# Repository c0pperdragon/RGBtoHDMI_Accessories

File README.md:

# RGBtoHDMI_Accessories

Some simple hardware parts to work together with the RGBtoHDMI.

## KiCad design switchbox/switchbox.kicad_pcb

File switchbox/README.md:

# Switchbox

Mechanical switchbox to select one of two 6-pin inputs to be forwarded to one Analog RGBtoHDMI.

Note that only the 3 color signals and the csync is switched. The GND and +5V pins are always 
connected through. Therefore do not connect two cables that provide their +5V to the RGBtoHDMI 
at the same time, as these would then be shorted together, which could damage either or 
both of the connected machines.

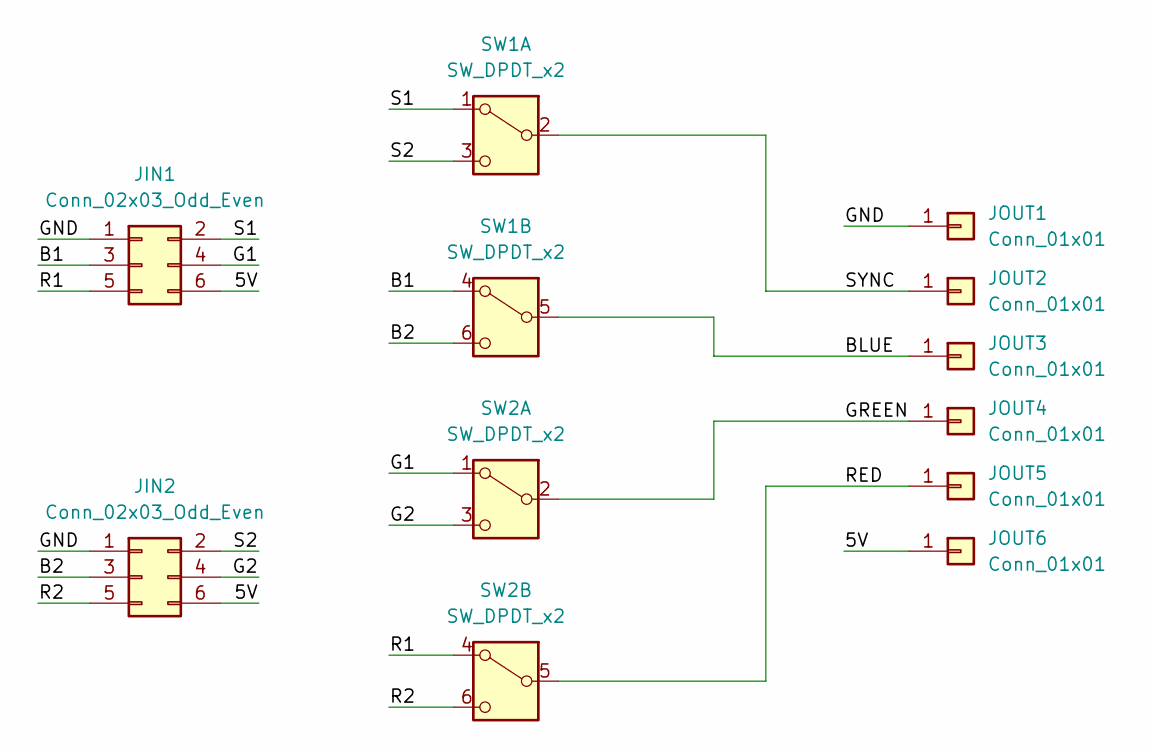
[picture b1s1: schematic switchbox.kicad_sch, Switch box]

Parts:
JIN1, JIN2: Conn_02x03_Odd_Even; IDC_PCB_mount_6
JOUT1, JOUT2, JOUT3, JOUT4, JOUT5, JOUT6: Conn_01x01; TestPoint_Pad_1.5x2.5mm
SW1, SW2: SW_DPDT_x2; OS202011MS2QN1

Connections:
/5V: JIN1.6, JIN2.6, JOUT6.1
/B1: JIN1.3, SW1.4 (A)
/B2: JIN2.3, SW1.6 (C)
/BLUE: JOUT3.1, SW1.5 (B)
/G1: JIN1.4, SW2.1 (A)
/G2: JIN2.4, SW2.3 (C)
/GND: JIN1.1, JIN2.1, JOUT1.1
/GREEN: JOUT4.1, SW2.2 (B)
/R1: JIN1.5, SW2.4 (A)
/R2: JIN2.5, SW2.6 (C)
/RED: JOUT5.1, SW2.5 (B)
/S1: JIN1.2, SW1.1 (A)
/S2: JIN2.2, SW1.3 (C)
/SYNC: JOUT2.1, SW1.2 (B)

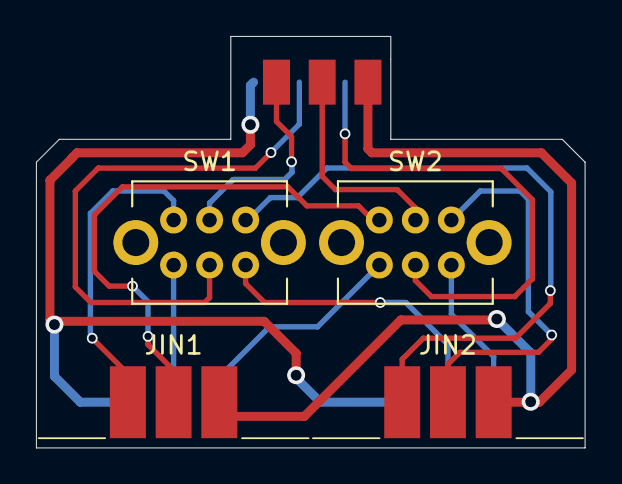
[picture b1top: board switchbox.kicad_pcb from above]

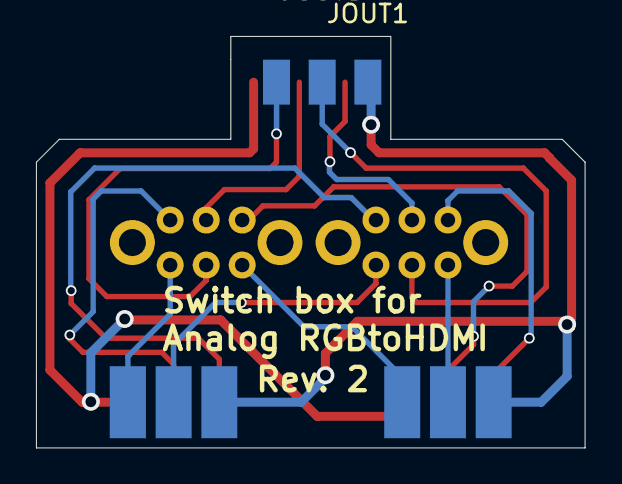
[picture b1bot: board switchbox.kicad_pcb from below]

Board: 2 copper layers, 30.5 x 22.9 mm, 10 parts (3 on the bottom side), 14 nets.

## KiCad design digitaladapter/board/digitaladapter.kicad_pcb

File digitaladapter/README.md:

# Digital adapter

This is a bridge from machines using a DB9 connector with
digital video output (MDA, CGA, EGA, C128) to the Analog RGBtoHDMI.

Up to 6 digital color signals are merged into 3 analog lines carrying one of 4 voltages. 
Separate sync signals are also XOR-merged to create composite sync.

For its active circuitry to work, it needs to draw a small amount of power
from the +5V pin of the 6-pin IDC connector. As this is normally not supported
by the RGBtoHDMI, one small modification is necessary to the analog board.

Until the offical RGBtoHDMI software directly provides working profiles, you need to 
add the files from 
[this archive](db9toanalog_extrafiles_2.zip)
to the installation.

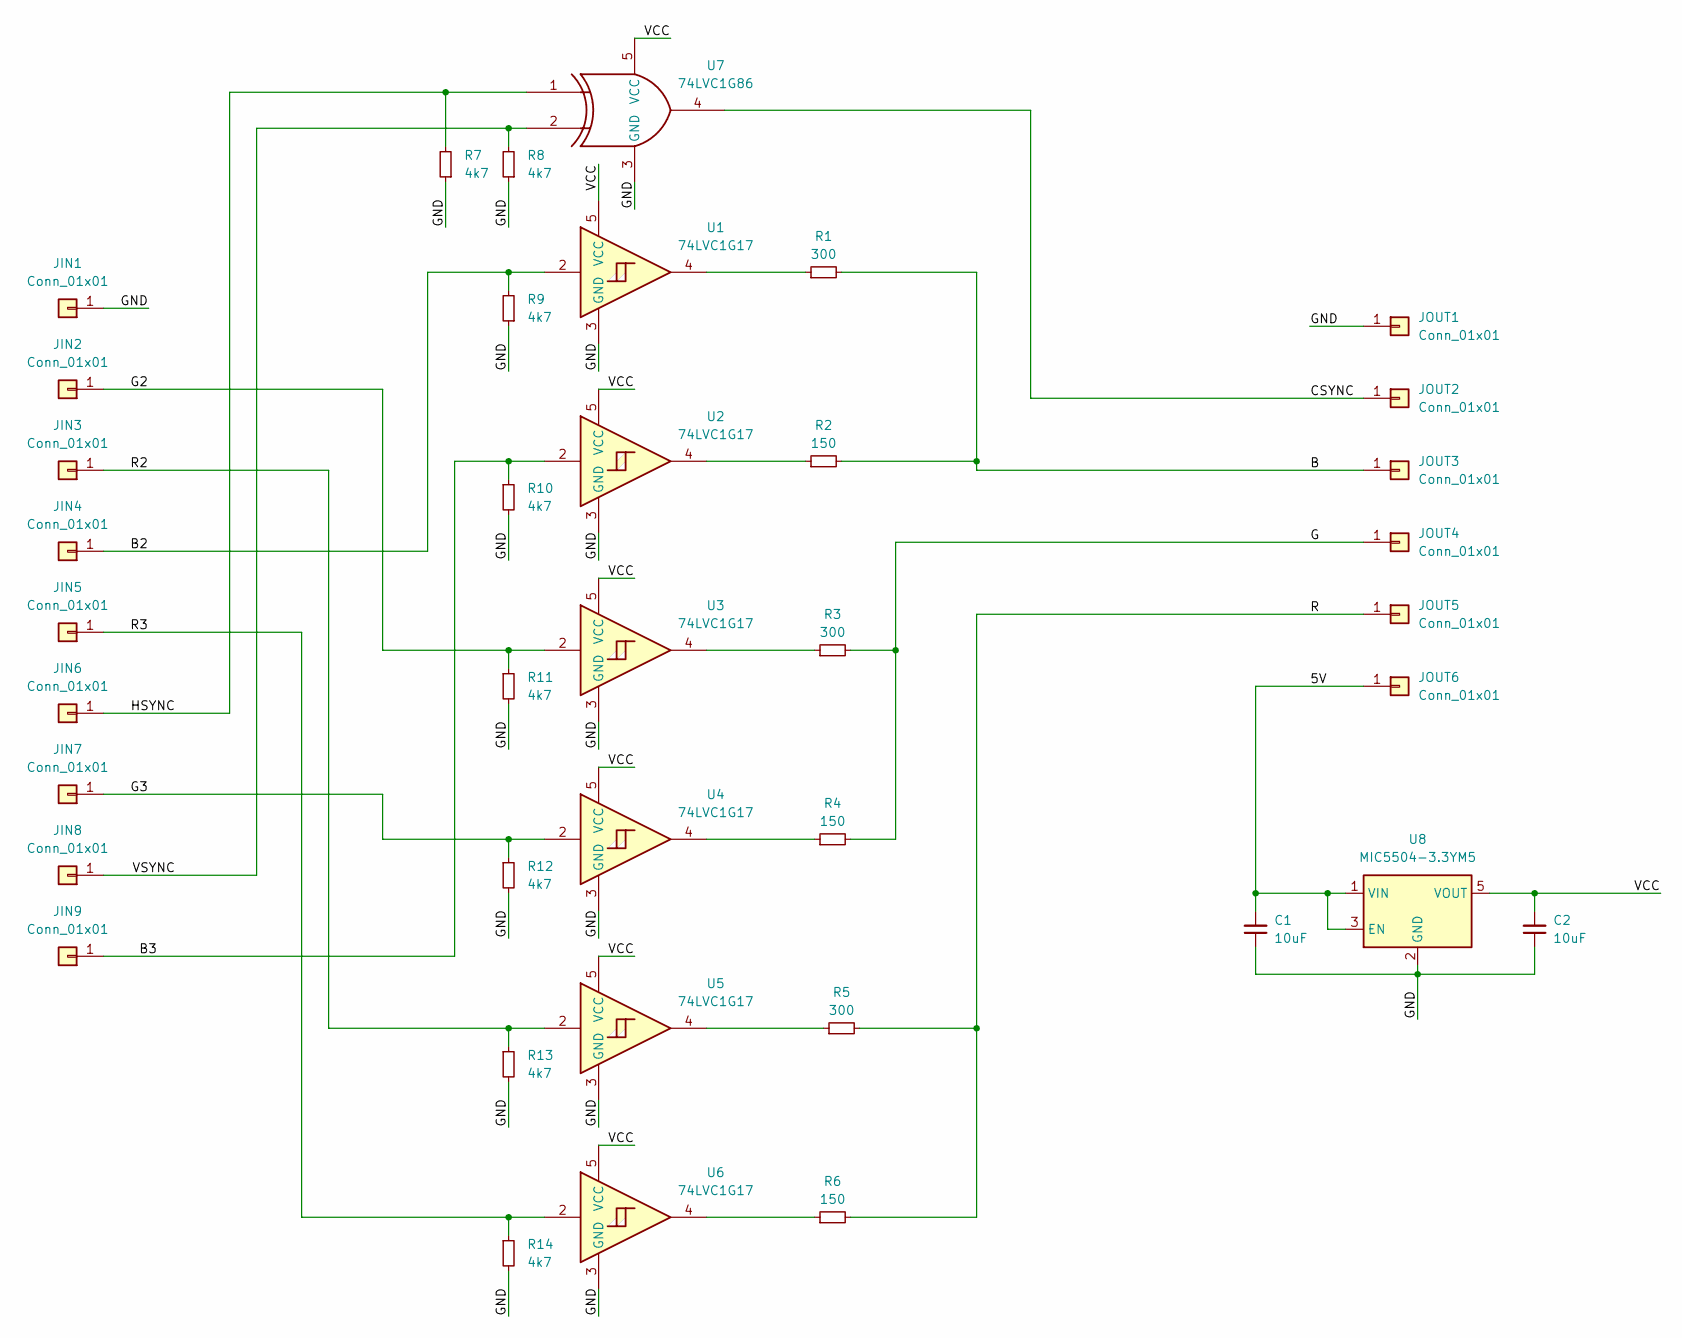
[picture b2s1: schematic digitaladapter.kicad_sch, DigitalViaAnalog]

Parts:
C1, C2: 10uF; C_0805_2012Metric
JIN1, JIN2, JIN3, JIN4, JIN5, JIN6, JIN7, JIN8, JIN9: Conn_01x01; TestPoint_Pad_2.5x1.5mm
JOUT1, JOUT2, JOUT3, JOUT4, JOUT5, JOUT6: Conn_01x01; TestPoint_Pad_2.5x1.5mm
R1, R3, R5: 300; R_0603_1608Metric
R2, R4, R6: 150; R_0603_1608Metric
R7, R8, R9, R10, R11, R12, R13, R14: 4k7; R_0603_1608Metric
U1, U2, U3, U4, U5, U6: 74LVC1G17; SOT-353_SC-70-5
U7: 74LVC1G86; SOT-353_SC-70-5
U8: MIC5504-3.3YM5; SOT-23-5

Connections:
/5V: C1.2, JOUT6.1, U8.1 (VIN), U8.3 (EN)
/B: JOUT3.1, R1.2, R2.2
/B2: JIN4.1, R9.2, U1.2
/B3: JIN9.1, R10.1, U2.2
/CSYNC: JOUT2.1, U7.4
/G: JOUT4.1, R3.2, R4.2
/G2: JIN2.1, R11.1, U3.2
/G3: JIN7.1, R12.1, U4.2
/GND: C1.1, C2.1, JIN1.1, JOUT1.1, R7.1, R8.1, R9.1, R10.2, R11.2, R12.2, R13.2, R14.2, U1.3 (GND), U2.3 (GND), U3.3 (GND), U4.3 (GND), U5.3 (GND), U6.3 (GND), U7.3 (GND), U8.2 (GND)
/HSYNC: JIN6.1, R7.2, U7.1
/R: JOUT5.1, R5.2, R6.2
/R2: JIN3.1, R13.1, U5.2
/R3: JIN5.1, R14.1, U6.2
/VCC: C2.2, U1.5 (VCC), U2.5 (VCC), U3.5 (VCC), U4.5 (VCC), U5.5 (VCC), U6.5 (VCC), U7.5 (VCC), U8.5 (VOUT)
/VSYNC: JIN8.1, R8.2, U7.2
unnamed: R1.1, U1.4
unnamed: R2.1, U2.4
unnamed: R3.1, U3.4
unnamed: R4.1, U4.4
unnamed: R5.1, U5.4
unnamed: R6.1, U6.4

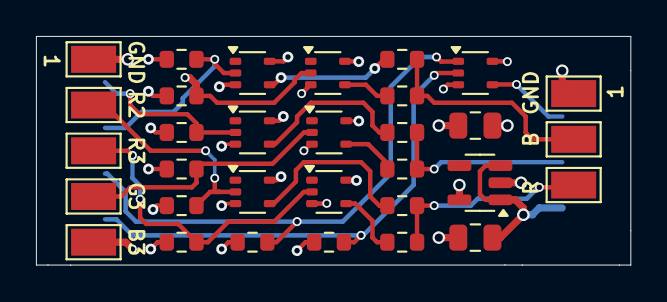
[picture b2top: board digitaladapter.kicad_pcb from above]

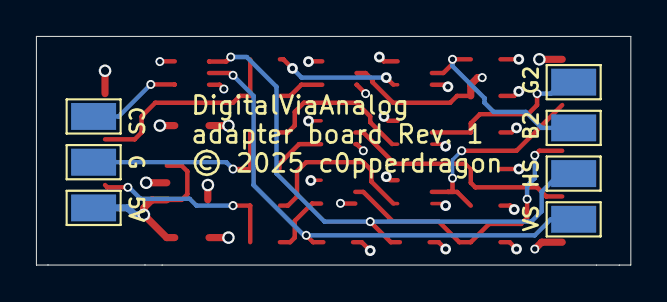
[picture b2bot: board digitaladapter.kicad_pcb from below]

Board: 4 copper layers, 33.0 x 12.7 mm, 39 parts (7 on the bottom side), 21 nets.

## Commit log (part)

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2025-10-07 Populate repro with pre-existing projects.
2025-10-07 Typos
2025-11-04 Provide profiles
2025-11-04 Restructure files
2025-11-14 Add C128 profile
2025-11-14 Fix clock rate for C128 profile
2025-12-09 Atari ST cable

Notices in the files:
digitaladapter/board/digitaladapter.kicad_pcb:
© 2025 c0pperdragon
